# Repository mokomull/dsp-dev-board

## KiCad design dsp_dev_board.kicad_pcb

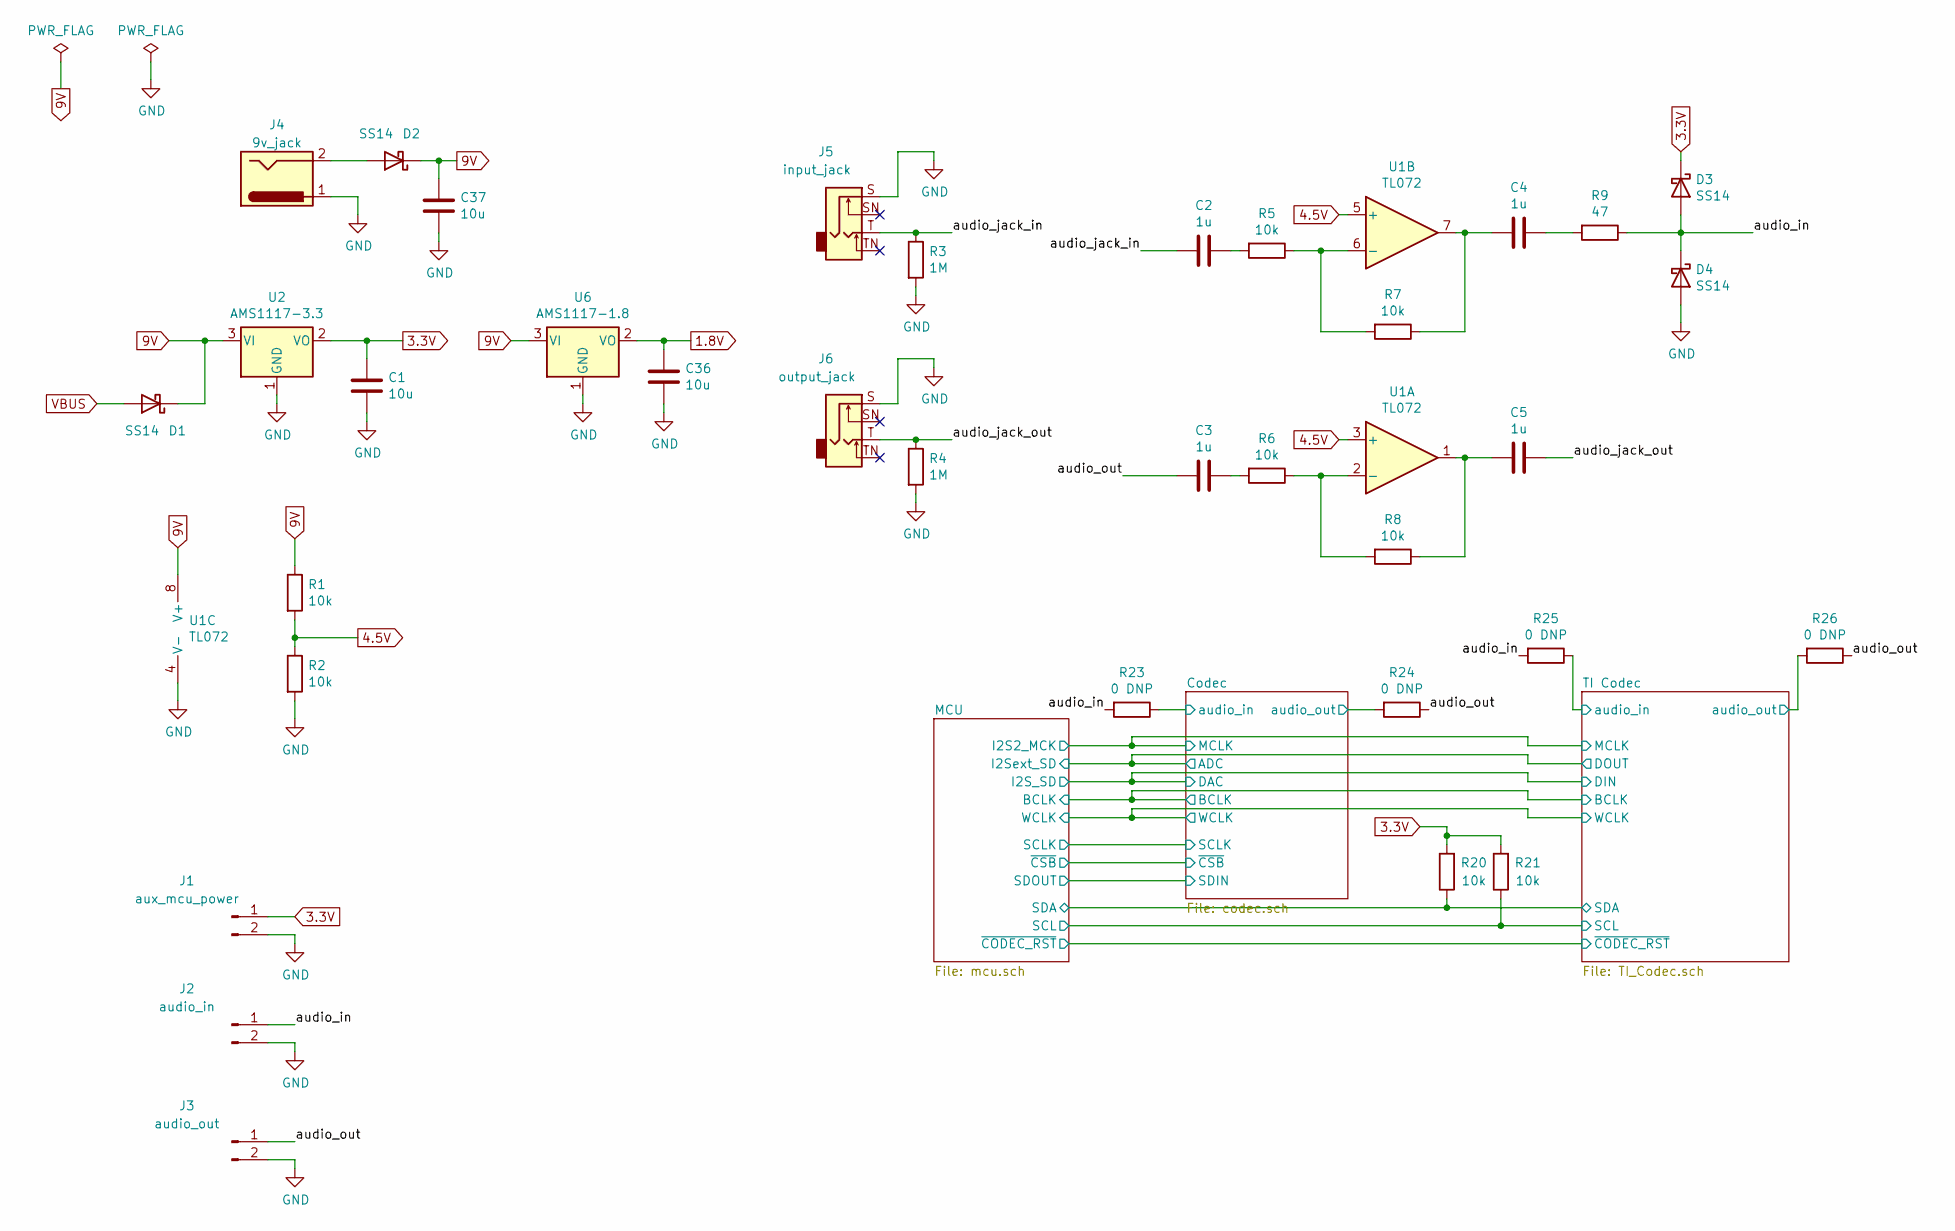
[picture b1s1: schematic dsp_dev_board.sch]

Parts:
C1, C36, C37: 10u; C_1206_3216Metric
C2, C3, C4, C5: 1u; C_0805_2012Metric
D1, D2, D3, D4: SS14; D_SMA
J1: aux_mcu_power; PinHeader_1x02_P2.54mm_Vertical
J2: audio_in; PinHeader_1x02_P2.54mm_Vertical
J3: audio_out; PinHeader_1x02_P2.54mm_Vertical
J4: 9v_jack; BarrelJack_Horizontal
J5: input_jack; Jack_6.35mm_Neutrik_NMJ4HCD2_Horizontal
J6: output_jack; Jack_6.35mm_Neutrik_NMJ4HCD2_Horizontal
R1, R2, R5, R6, R7, R8, R20, R21: 10k; R_0603_1608Metric
R3, R4: 1M; R_0603_1608Metric
R9: 47; R_0603_1608Metric
R23, R24, R25, R26: 0 DNP; R_0603_1608Metric
U1: TL072; SOIC-8_3.9x4.9mm_P1.27mm
U2: AMS1117-3.3; SOT-223-3_TabPin2
U6: AMS1117-1.8; SOT-223-3_TabPin2

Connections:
1.8V: C36.1, U6.2 (VO); also elsewhere on the board
3.3V: C1.1, D3.1 (K), J1.1, R20.2, R21.2, U2.2 (VO); also elsewhere on the board
4.5V: R1.2, R2.1, U1.3 (+), U1.5 (+)
9V: C37.1, D1.1 (K), D2.1 (K), R1.1, U1.8 (V+), U2.3 (VI), U6.3 (VI)
/Codec/audio_in: R23.1; also elsewhere on the board
/Codec/audio_out: R24.2; also elsewhere on the board
/MCU/SCL: R21.1; also elsewhere on the board
/MCU/SDA: R20.1; also elsewhere on the board
/TI Codec/audio_in: R25.1; also elsewhere on the board
/TI Codec/audio_out: R26.2; also elsewhere on the board
/audio_in: D3.2 (A), D4.1 (K), J2.1, R9.1, R23.2, R25.2
/audio_jack_in: C2.2, J5.T, R3.1
/audio_jack_out: C5.1, J6.T, R4.1
/audio_out: C3.2, J3.1, R24.1, R26.1
GND: C1.2, C36.2, C37.2, D4.2 (A), J1.2, J2.2, J3.2, J4.1, J5.S, J6.S, R2.2, R3.2, R4.2, U1.4 (V-), U2.1 (GND), U6.1 (GND); also elsewhere on the board
unnamed: C2.1, R5.2
unnamed: C3.1, R6.2
unnamed: C4.1, R9.2
unnamed: C4.2, R7.1, U1.7
unnamed: C5.2, R8.1, U1.1
unnamed: D2.2 (A), J4.2
unnamed: R5.1, R7.2, U1.6 (-)
unnamed: R6.1, R8.2, U1.2 (-)
VBUS: D1.2 (A); also elsewhere on the board

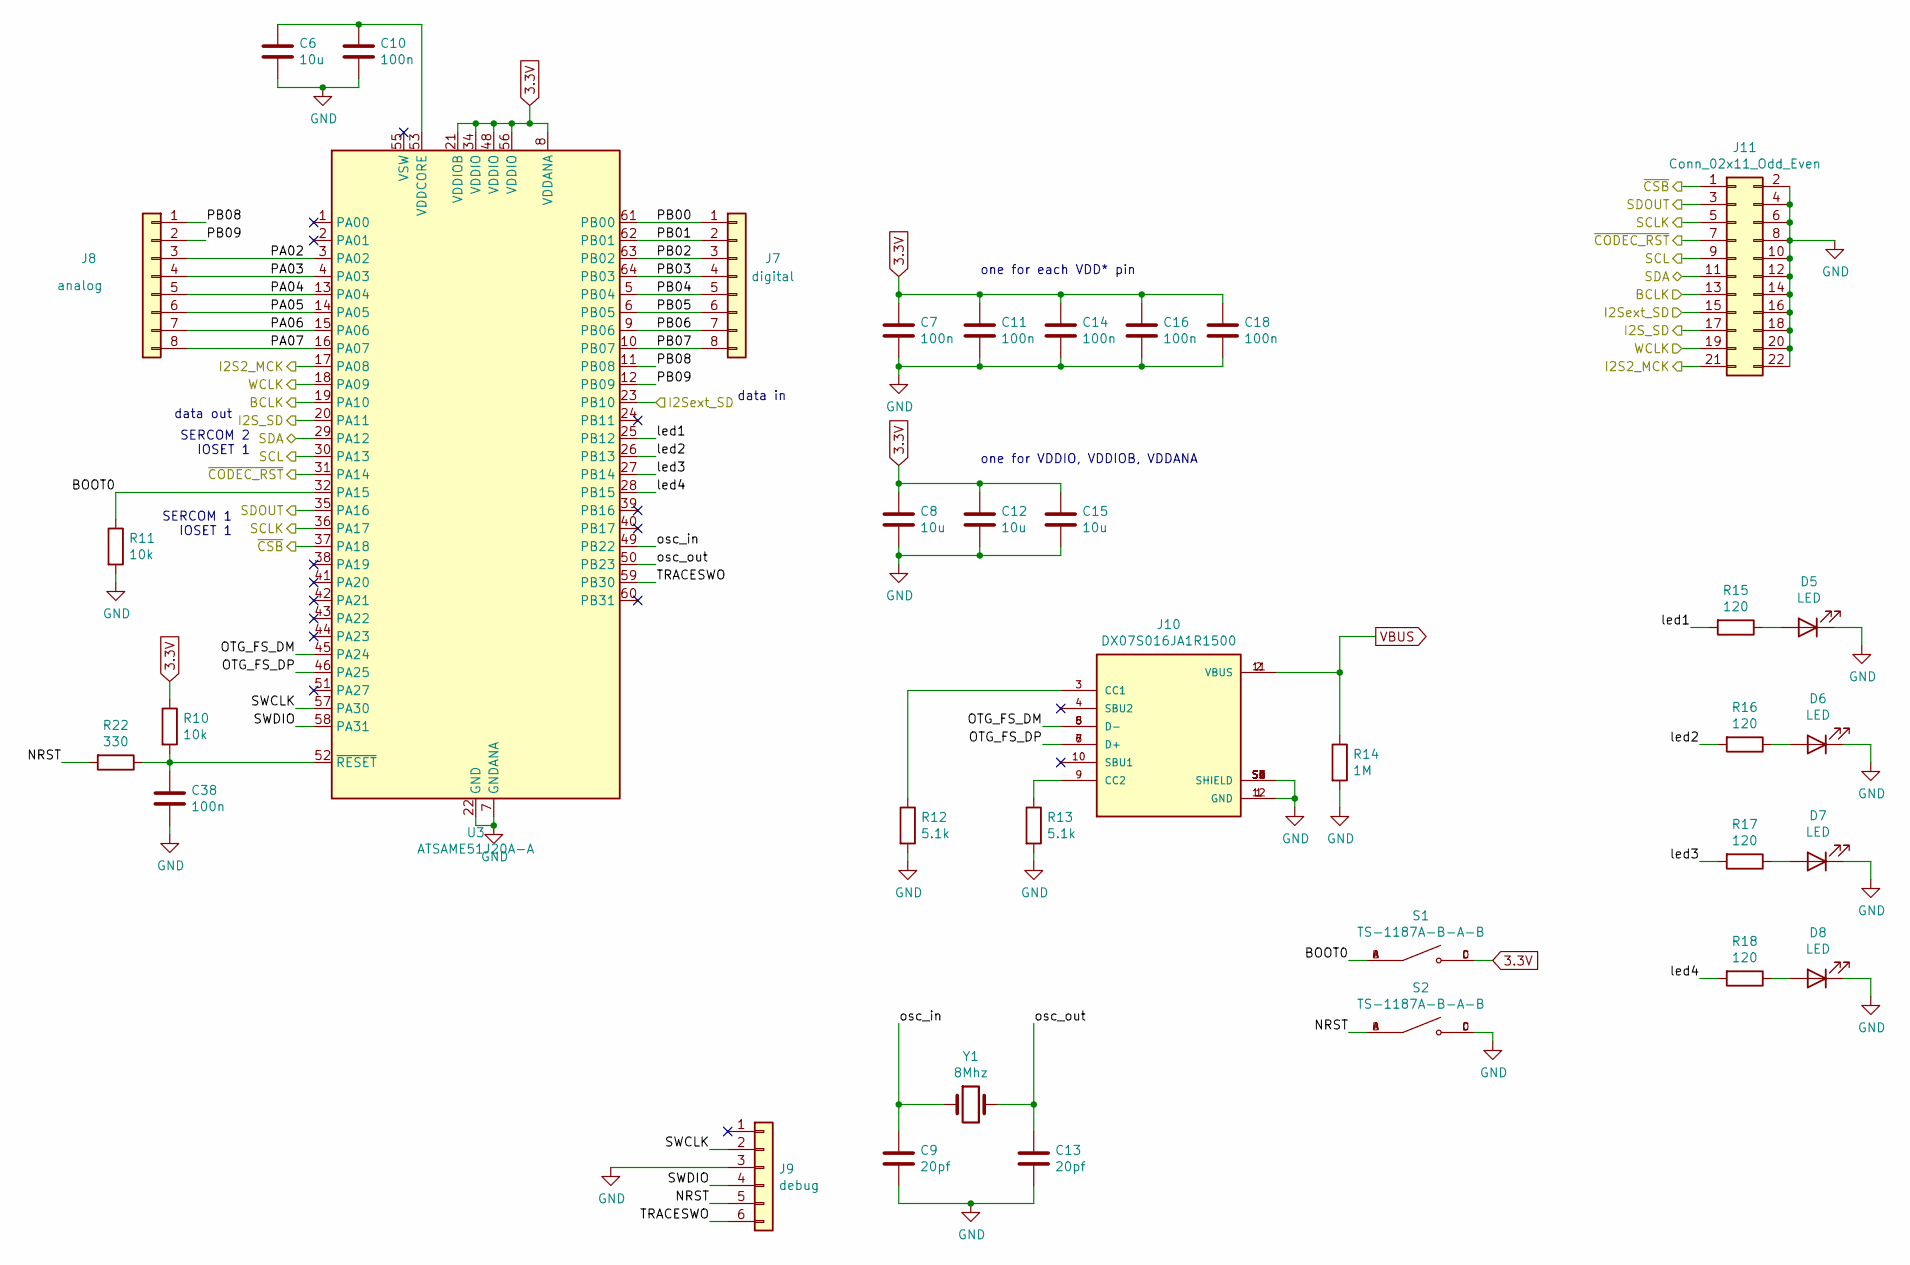
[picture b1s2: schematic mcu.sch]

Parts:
C6, C8, C12, C15: 10u; C_1206_3216Metric
C7, C10, C11, C14, C16, C18, C38: 100n; C_0603_1608Metric
C9, C13: 20pf; C_0603_1608Metric
D5, D6, D7, D8: LED; LED_0603_1608Metric
J7: digital; PinHeader_1x08_P2.54mm_Vertical
J8: analog; PinHeader_1x08_P2.54mm_Vertical
J9: debug; PinHeader_1x06_P2.54mm_Vertical
J10: DX07S016JA1R1500; JAE_DX07S016JA1R1500; PARTREV 1
J11: Conn_02x11_Odd_Even; PinHeader_2x11_P2.54mm_Vertical
R10, R11: 10k; R_0603_1608Metric
R12, R13: 5.1k; R_0603_1608Metric
R14: 1M; R_0603_1608Metric
R15, R16, R17, R18: 120; R_0603_1608Metric
R22: 330; R_0603_1608Metric
S1, S2: TS-1187A-B-A-B; SW_TS-1187A-B-A-B; PARTREV A0
U3: ATSAME51J20A-A; TQFP-64_10x10mm_P0.5mm
Y1: 8Mhz; Crystal_SMD_5032-2Pin_5.0x3.2mm

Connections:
3.3V: C7.1, C8.1, C11.1, C12.1, C14.1, C15.1, C16.1, C18.1, R10.1, S1.C, S1.D, U3.8 (VDDANA), U3.21 (VDDIOB), U3.34 (VDDIO), U3.48 (VDDIO), U3.56 (VDDIO); also elsewhere on the board
/Codec/ADC: J11.15, U3.23 (PB10); also elsewhere on the board
/Codec/BCLK: J11.13, U3.19 (PA10); also elsewhere on the board
/Codec/DAC: J11.17, U3.20 (PA11); also elsewhere on the board
/Codec/SCLK: J11.5, U3.36 (PA17); also elsewhere on the board
/Codec/SDIN: J11.3, U3.35 (PA16); also elsewhere on the board
/Codec/WCLK: J11.19, U3.18 (PA09); also elsewhere on the board
/Codec/~CSB: J11.1, U3.37 (PA18); also elsewhere on the board
/MCU/BOOT0: R11.1, S1.A, S1.B, U3.32 (PA15)
/MCU/I2S2_MCK: J11.21, U3.17 (PA08); also elsewhere on the board
/MCU/NRST: J9.5, R22.2, S2.A, S2.B
/MCU/OTG_FS_DM: J10.5 (D-), J10.8 (D-), U3.45 (PA24)
/MCU/OTG_FS_DP: J10.6 (D+), J10.7 (D+), U3.46 (PA25)
/MCU/PA02: J8.3, U3.3 (PA02)
/MCU/PA03: J8.4, U3.4 (PA03)
/MCU/PA04: J8.5, U3.13 (PA04)
/MCU/PA05: J8.6, U3.14 (PA05)
/MCU/PA06: J8.7, U3.15 (PA06)
/MCU/PA07: J8.8, U3.16 (PA07)
/MCU/PB00: J7.1, U3.61 (PB00)
/MCU/PB01: J7.2, U3.62 (PB01)
/MCU/PB02: J7.3, U3.63 (PB02)
/MCU/PB03: J7.4, U3.64 (PB03)
/MCU/PB04: J7.5, U3.5 (PB04)
/MCU/PB05: J7.6, U3.6 (PB05)
/MCU/PB06: J7.7, U3.9 (PB06)
/MCU/PB07: J7.8, U3.10 (PB07)
/MCU/PB08: J8.1, U3.11 (PB08)
/MCU/PB09: J8.2, U3.12 (PB09)
/MCU/SCL: J11.9, U3.30 (PA13); also elsewhere on the board
/MCU/SDA: J11.11, U3.29 (PA12); also elsewhere on the board
/MCU/SWCLK: J9.2, U3.57 (PA30)
/MCU/SWDIO: J9.4, U3.58 (PA31)
/MCU/TRACESWO: J9.6, U3.59 (PB30)
/MCU/led1: R15.2, U3.25 (PB12)
/MCU/led2: R16.2, U3.26 (PB13)
/MCU/led3: R17.2, U3.27 (PB14)
/MCU/led4: R18.2, U3.28 (PB15)
/MCU/osc_in: C9.1, U3.49 (PB22), Y1.1
/MCU/osc_out: C13.1, U3.50 (PB23), Y1.2
/MCU/~CODEC_RST: J11.7, U3.31 (PA14); also elsewhere on the board
GND: C6.2, C7.2, C8.2, C9.2, C10.2, C11.2, C12.2, C13.2, C14.2, C15.2, C16.2, C18.2, C38.2, D5.1 (K), D6.1 (K), D7.1 (K), D8.1 (K), J9.3, J10.1 (GND), J10.12 (GND), J10.S1 (SHIELD), J10.S2 (SHIELD), J10.S3 (SHIELD), J10.S4 (SHIELD), J10.S5 (SHIELD), J10.S6 (SHIELD), J11.2, J11.4, J11.6, J11.8, J11.10, J11.12, J11.14, J11.16, J11.18, J11.20, J11.22, R11.2, R12.2, R13.2, R14.2, S2.C, S2.D, U3.7 (GNDANA), U3.22 (GND), U3.33 (GND), U3.47 (GND), U3.54 (GND); also elsewhere on the board
unnamed: C6.1, C10.1, U3.53 (VDDCORE)
unnamed: C38.1, R10.2, R22.1, U3.52 (~RESET)
unnamed: D5.2 (A), R15.1
unnamed: D6.2 (A), R16.1
unnamed: D7.2 (A), R17.1
unnamed: D8.2 (A), R18.1
unnamed: J10.3 (CC1), R12.1
unnamed: J10.9 (CC2), R13.1
VBUS: J10.2 (VBUS), J10.11 (VBUS), R14.1; also elsewhere on the board

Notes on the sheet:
data out
data in
one for each VDD* pin
one for VDDIO, VDDIOB, VDDANA
SERCOM 1 IOSET 1
SERCOM 2 IOSET 1

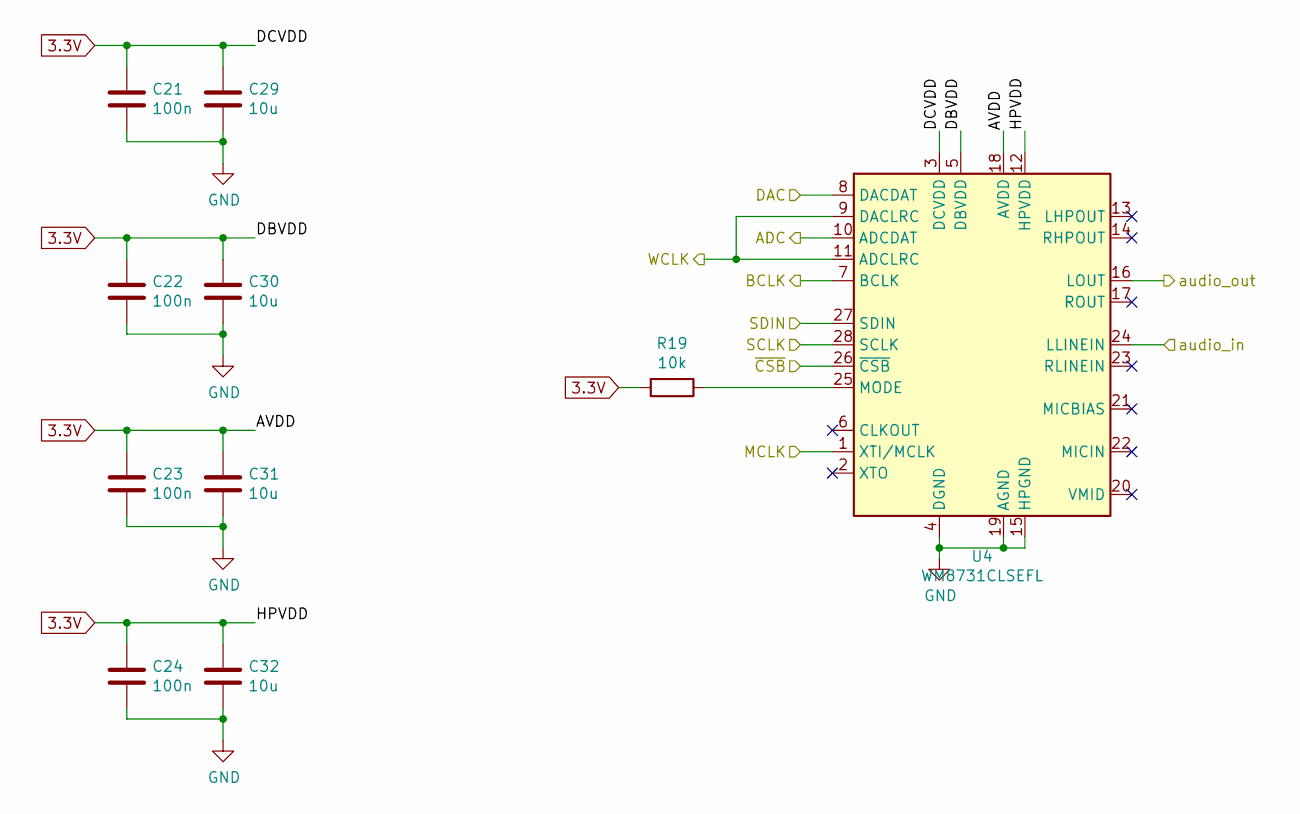
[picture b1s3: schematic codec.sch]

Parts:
C21, C22, C23, C24: 100n; C_0603_1608Metric
C29, C30, C31, C32: 10u; C_1206_3216Metric
R19: 10k; R_0603_1608Metric
U4: WM8731CLSEFL; QFN-28-1EP_5x5mm_P0.5mm_EP3.35x3.35mm

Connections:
3.3V: C21.1, C22.1, C23.1, C24.1, C29.1, C30.1, C31.1, C32.1, R19.2, U4.3 (DCVDD), U4.5 (DBVDD), U4.12 (HPVDD), U4.18 (AVDD); also elsewhere on the board
/Codec/ADC: U4.10 (ADCDAT); also elsewhere on the board
/Codec/BCLK: U4.7 (BCLK); also elsewhere on the board
/Codec/DAC: U4.8 (DACDAT); also elsewhere on the board
/Codec/SCLK: U4.28 (SCLK); also elsewhere on the board
/Codec/SDIN: U4.27 (SDIN); also elsewhere on the board
/Codec/WCLK: U4.9 (DACLRC), U4.11 (ADCLRC); also elsewhere on the board
/Codec/audio_in: U4.24 (LLINEIN); also elsewhere on the board
/Codec/audio_out: U4.16 (LOUT); also elsewhere on the board
/Codec/~CSB: U4.26 (~CSB); also elsewhere on the board
/MCU/I2S2_MCK: U4.1 (XTI/MCLK); also elsewhere on the board
GND: C21.2, C22.2, C23.2, C24.2, C29.2, C30.2, C31.2, C32.2, U4.4 (DGND), U4.15 (HPGND), U4.19 (AGND), U4.29 (AGND); also elsewhere on the board
unnamed: R19.1, U4.25 (MODE)

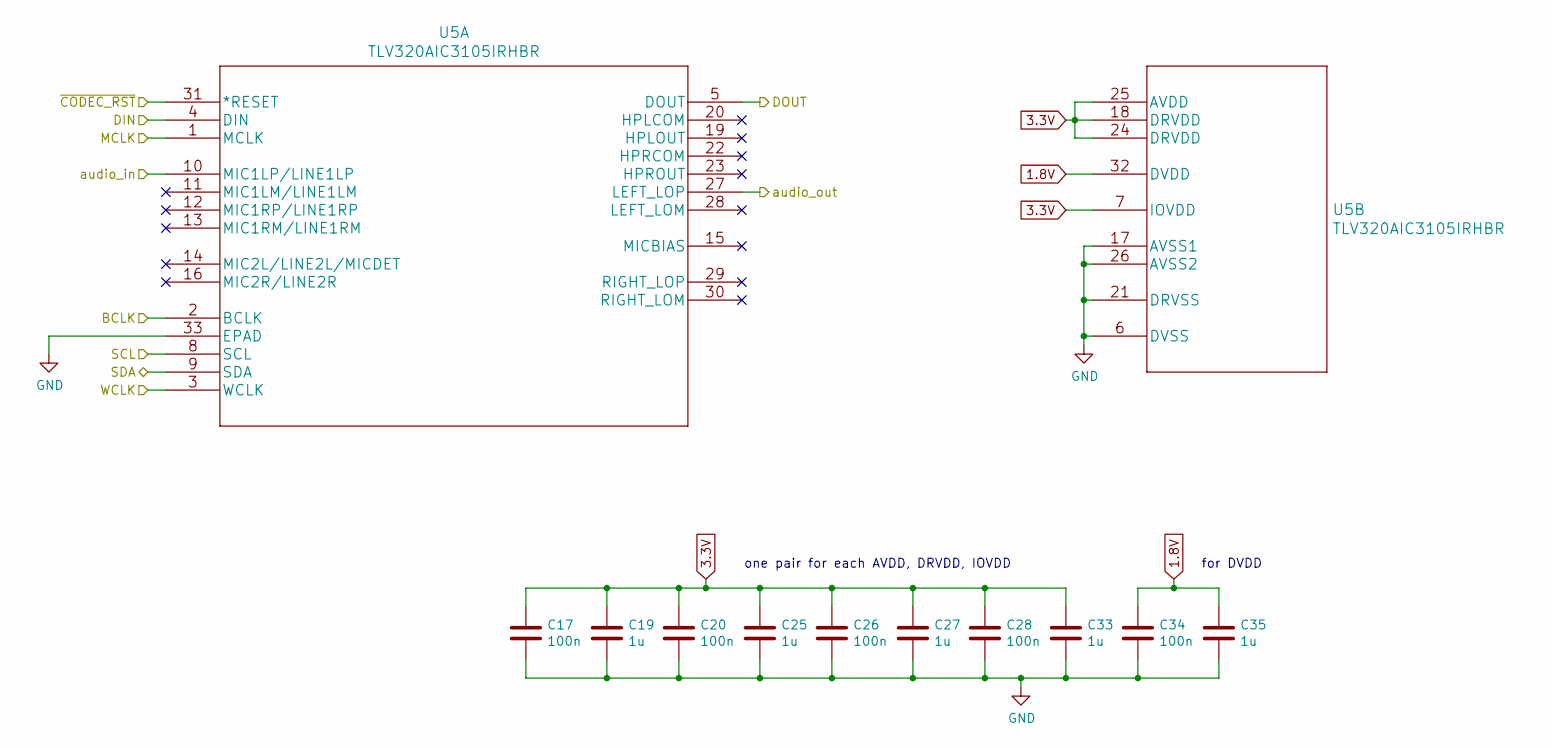
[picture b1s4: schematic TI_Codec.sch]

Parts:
C17, C20, C26, C28, C34: 100n; C_0603_1608Metric
C19, C25, C27, C33, C35: 1u; C_0805_2012Metric
U5: TLV320AIC3105IRHBR; QFN-32-1EP_5x5mm_P0.5mm_EP3.45x3.45mm_ThermalVias

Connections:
1.8V: C34.1, C35.1, U5.32 (DVDD); also elsewhere on the board
3.3V: C17.1, C19.1, C20.1, C25.1, C26.1, C27.1, C28.1, C33.1, U5.7 (IOVDD), U5.18 (DRVDD), U5.24 (DRVDD), U5.25 (AVDD); also elsewhere on the board
/Codec/ADC: U5.5 (DOUT); also elsewhere on the board
/Codec/BCLK: U5.2 (BCLK); also elsewhere on the board
/Codec/DAC: U5.4 (DIN); also elsewhere on the board
/Codec/WCLK: U5.3 (WCLK); also elsewhere on the board
/MCU/I2S2_MCK: U5.1 (MCLK); also elsewhere on the board
/MCU/SCL: U5.8 (SCL); also elsewhere on the board
/MCU/SDA: U5.9 (SDA); also elsewhere on the board
/MCU/~CODEC_RST: U5.31 (*RESET); also elsewhere on the board
/TI Codec/audio_in: U5.10 (MIC1LP/LINE1LP); also elsewhere on the board
/TI Codec/audio_out: U5.27 (LEFT_LOP); also elsewhere on the board
GND: C17.2, C19.2, C20.2, C25.2, C26.2, C27.2, C28.2, C33.2, C34.2, C35.2, U5.6 (DVSS), U5.17 (AVSS1), U5.21 (DRVSS), U5.26 (AVSS2), U5.33 (EPAD); also elsewhere on the board

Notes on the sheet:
one pair for each AVDD, DRVDD, IOVDD
for DVDD

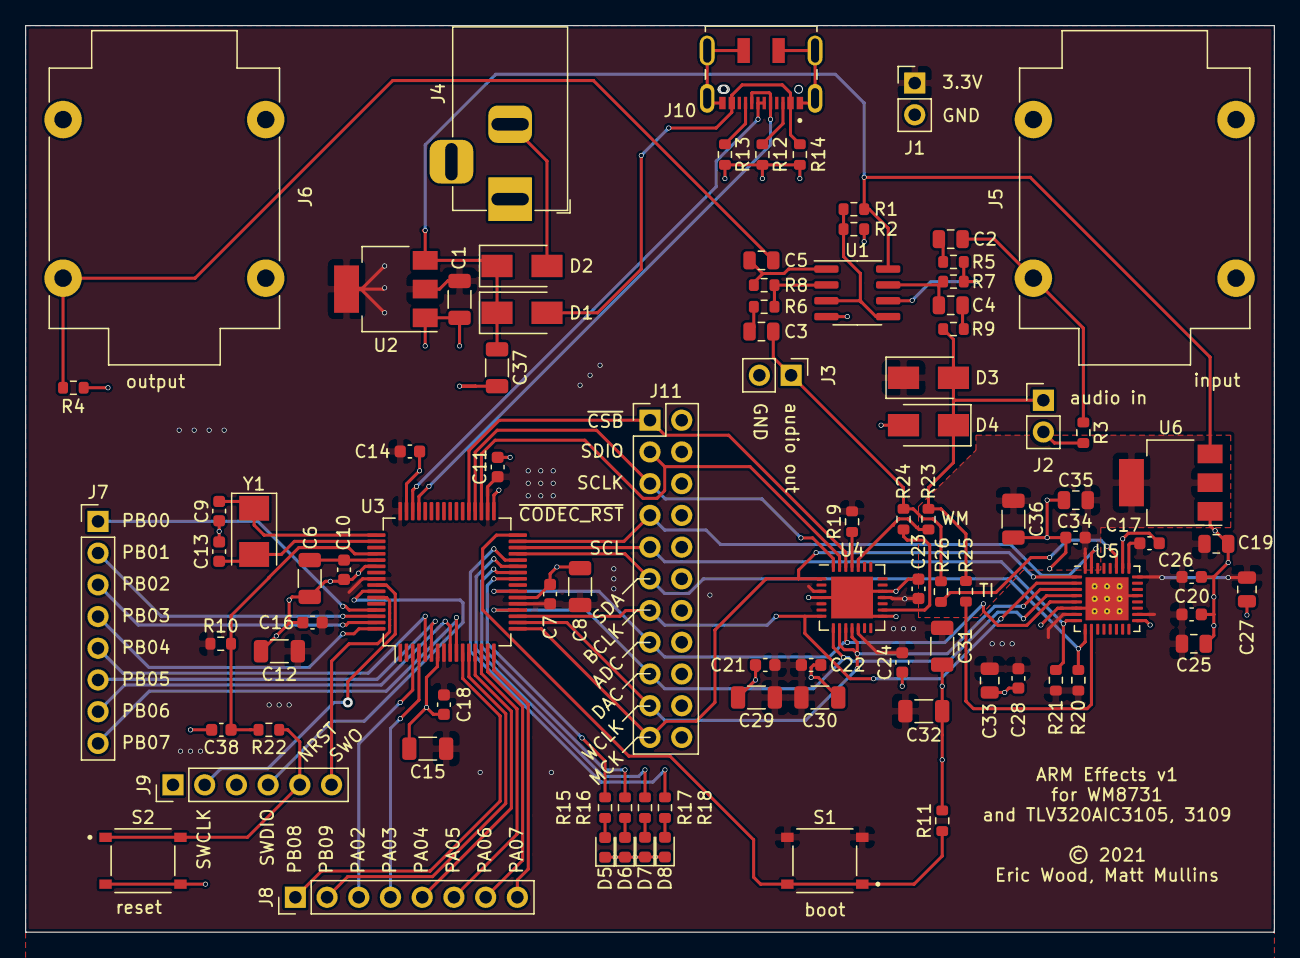
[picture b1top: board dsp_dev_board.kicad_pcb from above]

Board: 4 copper layers, 100.0 x 72.6 mm, 92 parts (0 on the bottom side), 71 nets.

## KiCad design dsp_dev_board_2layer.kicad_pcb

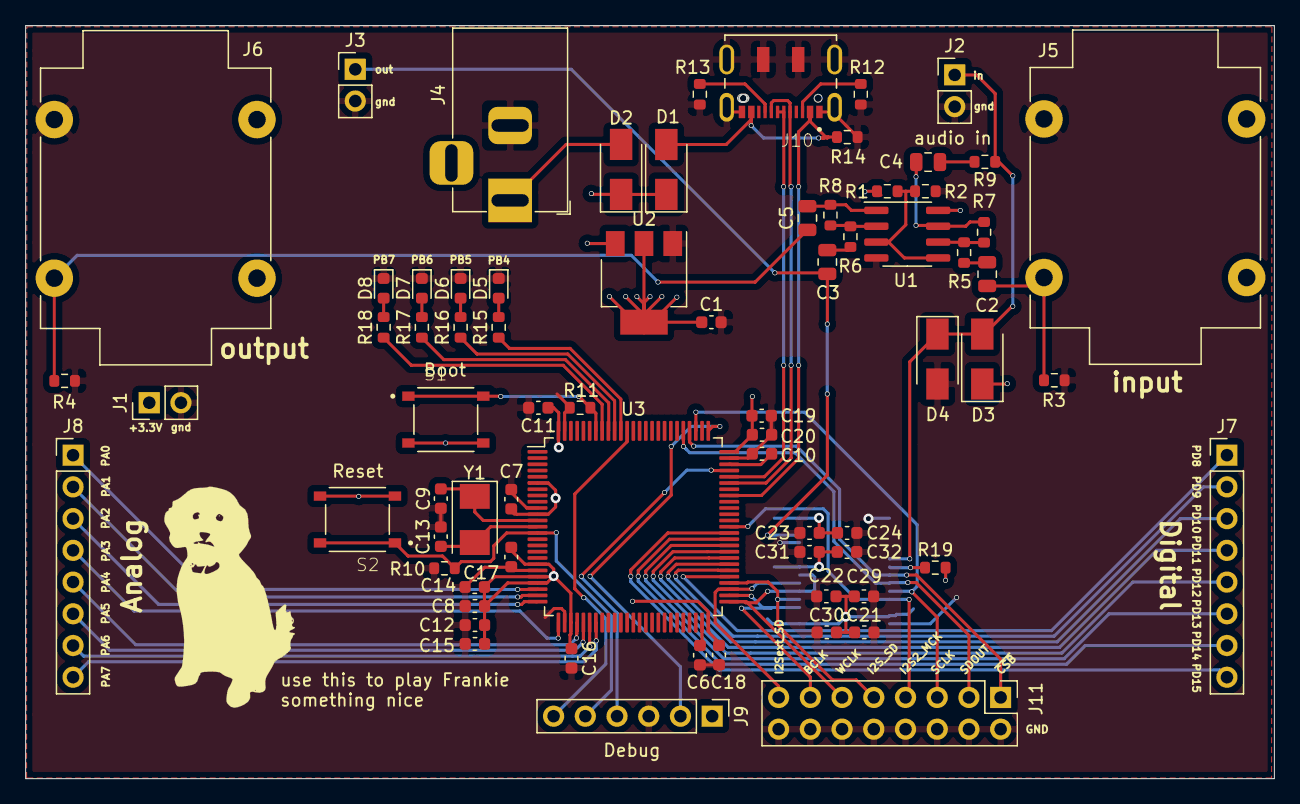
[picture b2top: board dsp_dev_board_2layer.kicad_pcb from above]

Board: 2 copper layers, 100.0 x 60.3 mm, 73 parts (1 on the bottom side), 63 nets.

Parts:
C1, C21, C22, C23, C24: 0.1u; C_0603_1608Metric
C2, C3, C4, C5: 1u; C_0805_2012Metric
C6, C10: 2.2u; C_0603_1608Metric
C7, C11, C12, C14, C16, C17, C18, C19: 100n; C_0603_1608Metric
C8, C15: 1u; C_0603_1608Metric
C9, C13: 20pf; C_0603_1608Metric
C20: 4.7u; C_0603_1608Metric
C29, C30, C31, C32: 10u; C_0603_1608Metric
D1, D2, D3, D4: SS14; D_SMA
D5, D6, D7, D8: LED; LED_0603_1608Metric
J1: aux_mcu_power; PinHeader_1x02_P2.54mm_Vertical
J2: audio_in; PinHeader_1x02_P2.54mm_Vertical
J3: audio_out; PinHeader_1x02_P2.54mm_Vertical
J4: 9v_jack; BarrelJack_Horizontal
J5: input_jack; Jack_6.35mm_Neutrik_NMJ4HCD2_Horizontal
J6: output_jack; Jack_6.35mm_Neutrik_NMJ4HCD2_Horizontal
J7: PD8-15 (digital); PinHeader_1x08_P2.54mm_Vertical
J8: PA0-7 (analog); PinHeader_1x08_P2.54mm_Vertical
J9: debug; PinHeader_1x06_P2.54mm_Vertical
J10: DX07S016JA1R1500; JAE_DX07S016JA1R1500
J11: Conn_02x08_Odd_Even; PinHeader_2x08_P2.54mm_Vertical
R1, R2, R5, R6, R7, R8, R10, R11, R19: 10k; R_0603_1608Metric
R3, R4, R14: 1M; R_0603_1608Metric
R9: 47; R_0603_1608Metric
R12, R13: 5.1k; R_0603_1608Metric
R15, R16, R17, R18: 120; R_0603_1608Metric
S1, S2: TS-1187A-B-A-B; SW_TS-1187A-B-A-B
U1: TL072; SOIC-8_3.9x4.9mm_P1.27mm
U2: AMS1117-3.3; SOT-223-3_TabPin2
U3: STM32F407VETx; LQFP-100_14x14mm_P0.5mm
U4: WM8731SEDS; SSOP-28_5.3x10.2mm_P0.65mm
Y1: 8Mhz; Crystal_SMD_5032-2Pin_5.0x3.2mm

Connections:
3.3V: C1.1, C7.1, C8.1, C11.1, C12.1, C14.1, C15.1, C16.1, C17.1, C18.1, C19.1, C20.1, C21.1, C22.1, C23.1, C24.1, C29.1, C30.1, C31.1, C32.1, D3.1, J1.1, R19.2, S1.C, S1.D, S2.C, S2.D, U2.2, U3.6, U3.11, U3.19, U3.21, U3.22, U3.28, U3.50, U3.75, U3.100, U4.1, U4.8, U4.14, U4.27
4.5V: R1.2, R2.1, U1.3, U1.5
9V: D1.1, D2.1, R1.1, U1.8, U2.3
/Codec/ADC: J11.15, U3.53, U4.6
/Codec/BCLK: J11.13, U3.52, U4.3
/Codec/DAC: J11.9, U3.54, U4.4
/Codec/SCLK: J11.5, U3.78, U4.24
/Codec/SDIN: J11.3, U3.80, U4.23
/Codec/WCLK: J11.11, U3.51, U4.5, U4.7
/Codec/~CSB: J11.1, U3.79, U4.22
/MCU/BOOT0: R11.1, S1.A, S1.B, U3.94
/MCU/I2S2_MCK: J11.7, U3.63, U4.25
/MCU/NRST: J9.5, R10.1, S2.A, S2.B, U3.14
/MCU/OTG_FS_DM: J10.5, J10.8, U3.70
/MCU/OTG_FS_DP: J10.6, J10.7, U3.71
/MCU/SWCLK: J9.2, U3.76
/MCU/SWDIO: J9.4, U3.72
/MCU/TRACESWO: J9.6, U3.89
/MCU/VCAP_1: C6.1, U3.49
/MCU/VCAP_2: C10.1, U3.73
/MCU/led1: R15.2, U3.90
/MCU/led2: R16.2, U3.91
/MCU/led3: R17.2, U3.92
/MCU/led4: R18.2, U3.93
/MCU/osc_in: C9.1, U3.12, Y1.1
/MCU/osc_out: C13.1, U3.13, Y1.2
/audio_in: D3.2, D4.1, J2.1, R9.1, U4.20
/audio_jack_in: C2.2, J5.T, R3.1
/audio_jack_out: C5.1, J6.T, R4.1
/audio_out: C3.2, J3.1, U4.12
GND: C1.2, C6.2, C7.2, C8.2, C9.2, C10.2, C11.2, C12.2, C13.2, C14.2, C15.2, C16.2, C17.2, C18.2, C19.2, C20.2, C21.2, C22.2, C23.2, C24.2, C29.2, C30.2, C31.2, C32.2, D4.2, D5.1, D6.1, D7.1, D8.1, J1.2, J2.2, J3.2, J4.2, J5.S, J6.S, J9.3, J10.1, J10.12, J10.S1, J10.S2, J10.S3, J10.S4, J10.S5, J10.S6, J11.2, J11.4, J11.6, J11.8, J11.10, J11.12, J11.14, J11.16, R2.2, R3.2, R4.2, R10.2, R11.2, R12.2, R13.2, R14.2, U1.4, U2.1, U3.10, U3.20, U3.27, U3.74, U3.99, U4.11, U4.15, U4.28
unnamed: C2.1, R5.2
unnamed: C3.1, R6.2
unnamed: C4.1, R9.2
unnamed: C4.2, R7.1, U1.7
unnamed: C5.2, R8.1, U1.1
unnamed: D2.2, J4.1
unnamed: D5.2, R15.1
unnamed: D6.2, R16.1
unnamed: D7.2, R17.1
unnamed: D8.2, R18.1
unnamed: J7.1, U3.55
unnamed: J7.2, U3.56
unnamed: J7.3, U3.57
unnamed: J7.4, U3.58
unnamed: J7.5, U3.59
unnamed: J7.6, U3.60
unnamed: J7.7, U3.61
unnamed: J7.8, U3.62
unnamed: J8.1, U3.23
unnamed: J8.2, U3.24
unnamed: J8.3, U3.25
unnamed: J8.4, U3.26
unnamed: J8.5, U3.29
unnamed: J8.6, U3.30
unnamed: J8.7, U3.31
unnamed: J8.8, U3.32
unnamed: J10.3, R12.1
unnamed: J10.9, R13.1
unnamed: R5.1, R7.2, U1.6
unnamed: R6.1, R8.2, U1.2
unnamed: R19.1, U4.21
VBUS: D1.2, J10.2, J10.11, R14.1, U3.68

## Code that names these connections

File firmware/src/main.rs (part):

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    let pins = atsamd_hal::gpio::v2::Pins::new(peripherals.PORT);

    let control_pads = spi::Pads::<Sercom1, IoSet1>::new()
        .data_out::<Pad0, _>(pins.pa16)
        .sclk(pins.pa17);

    let control_spi = spi::Config::new(
        &mut peripherals.MCLK,
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    .baud(100.khz())
    .enable();

    let control_csb = pins.pa18.into_push_pull_output();

    let mut control = Control {
        spi: control_spi,
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    // enable output
    control.set_register(WM8731::power_down(final_power_settings));

    let _mck = pins.pa08.into_alternate::<J>();
    let _sck = pins.pa10.into_alternate::<J>();
    let _dac = pins.pa11.into_alternate::<J>();
    let _ws = pins.pa09.into_alternate::<J>();

    let i2s = peripherals.I2S;
    i2s.clkctrl[0].write(|w| {
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
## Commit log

2021-01-14 Initial commit, power section seems ok?
2021-01-15 Add codec symbol
2021-01-17 Wire up codec
2021-01-17 Hook up peripherals
2021-01-17 Add debug header
2021-01-18 Use a better codec
2021-01-20 Power the MCU
2021-01-24 Coupling caps, crystals
2021-01-24 Clean things up, add LEDs, aux stuff
2021-02-13 Various fixes
2021-02-13 Add debug interface
2021-02-13 Add traces
2021-02-14 Use contiguous GPIO pins
2021-02-14 Improved probe points
2021-02-14 Assign a bunch of footprints
2021-02-14 Add tactile switch footprints
2021-02-14 Move switch library here
2021-02-14 Add USB connector
2021-02-14 unfuck symbols
2021-02-14 maybe this will work
2021-02-14 make routing easier
2021-02-14 Update pins for actual ADC ins
2021-02-15 those two need to be connected
2021-02-27 just a buncha stuff
2021-02-28 Progress
2021-02-28 USB to go
2021-02-28 Lots of cleanup
2021-03-07 Basically done?
2021-03-07 it's done
2021-04-13 4 layer progress
2021-04-13 mcu.sch: replace microcontroller with SAME51J
    The I2S bus is placed according to IOSET 1.
    The ADC inputs are sprinkled around mostly-arbitrarily, but since
    PA00-01 are not connected to either ADC peripheral, this uses PB08-09
    for those two signals. PB08 and 09 are connected to *both* ADCs, so
    they should be sampleable simultaneously if necessary.
2021-04-15 Wire up SPI control, add TLV320AIC310x and I2C
    The I2C is convenient: if I got it backwards, the SDA and SCL pins are
    reversed between SERCOM 2 and 4.
2021-04-15 Add pull-up resistors for I2C
2021-04-15 mcu: swap 4.7u VDDCORE cap (C6) for 10u
    There's already 10u all over the board so why not squeeze a bit more out
    of the BOM.
    Also adds a footprint for the 100n next to it (C10).
2021-04-15 Apply footprint-finder's suggestion for USB-C
    It likes the USB_C: prefix, I guess.
2021-04-15 "0.1u" -> "100n"; use 1206 10u for bulk decoupling
    The 1206 size has a much better derating-vs-bias-voltage curve.
2021-04-15 Add a 10u decoupling for the main 9V supply
2021-04-15 Wire up more internal buses to the debug connector
    It'll be nice to scope the I2C bus as well.
2021-04-15 Add RC to NRST for timing
    The Schematic Checklist, §60.4 "External Reset Circuit" told me to do
    it.
2021-04-15 re-import USB-C connector
2021-04-16 sch: add jumpers to select audio path
    This way the unused codec's audio path won't be dangling as an antenna
    picking up unnecessary noise on the analog side
2021-04-19 Add TI codec schematic page.
    This has actually already gone through a couple revisions, but I never
    added it to git. Oops.
2021-04-19 PCB: most major layout with both codec footprints
    Surprisingly, I don't hate the really long I2S bus-like formation
    between both footprints, though it does break up both the front and back
    layers in the same orientation.
2021-04-19 Annotate schematic symbols
    I forgot to do this when I added the jumper resistors.
2021-04-19 PCB: update TI's footprint so thermal vias are GND
    They were numbered "V" which KiCad thought should be a different net,
    throwing all sorts of DRC errors. Numbering them all 33 makes it act
    like the built-in footprint with thermal vias.
2021-04-21 Use actual parts from Mouser order
    I was able to order the ATSAME51J20A-AU and the WM8731CLSEFL.
2021-04-24 WIP: QFN all the things
2021-04-29 pcb: everything connected, passes DRC
2021-04-29 pcb: enhance bypassing on the left side of MCU
    I stuck the bulk bypassing for VDDIO near pin 56, so nudge those
    capacitors over so the F.Cu layer can connect them, and stitch that
    through with some vias to the B.Cu +3.3V rail.
2021-04-29 pcb: nudge stuff around so it looks good
2021-04-29 pcb: move silkscreens so they're visible
    Component references should not be over vias or other parts. Move them
    so they're visible, but maintain orientation -- the label is vertical if
    the component is vertical.
2021-04-29 pcb: add silkscreens
    This labels the pins for the analog, digital, debug, and probepoint
    headers. I also moved R10 so I could have more room for the digital
    header labels.
2021-04-30 pcb: move silkscreen for C1 and C26
    They were under other components.
2021-04-30 pcb: minor movements, add more labels
    more silkscreens, move some traces
2021-04-30 Swap TI codec footprint for builtin QFN
    5x5mm size, 0.5mm pitch, 3.45mm exposed pad. TI recommends the thermal
    vias, though on something this low-power, I think that's overkill.
    I had to use a copper-fill keepout and manually draw traces to keep the
    pads from being horribly misshaped.
2021-04-30 pcb: move more silkscreens
    I moved C17, so its silkscreen ended up under C19.
    Label the jumpers for WM and TI codecs (and abbreviate to WM because
    "WM8731" doesn't fit in the space I have)
2021-04-30 power should be center-negative
    And add attribution text to the PCB
2021-04-30 add boot/reset labels for the switches
2021-04-30 fab: add fab files from first board order
2021-05-18 firmware: cortex-m-quickstart + empty loop
    This seems to work!
2021-05-18 firmware: blink LED1 at 2Hz
    It works!
2021-05-19 fw: blink all LEDs in order
2021-05-19 fw: send "hello, world." over SPI
    This will be the configuration channel for the WM8731 codec.
2021-05-19 fw: transmit bit pattern with I2S
    This results in a jittery, but exactly 12.288MHz MCLK, and 48.000kHz
    WCLK.
2021-05-19 fw: import WM8731 configuration from echo_pedal
    This is pretty much an exact copy/paste from the echo-pedal experiment,
    with `use` glue to make the names match up exactly as written
    previously.
    It does not quite work, though.
2021-05-31 fw: work around not-actually-blocking SPI impl
    The atsamd_hal blocking SPI implementation blocks until it's in the
    FIFO, not until it's been transmitted. This results in #CS being
    deasserted way too early for the first command, so instead just wait
    long enough to get the command out.
2021-05-31 fw: mono mode still needs txdata to be written
    It seems to ignore the 0 written here (verified with an oscilloscope),
    and does dutifully copy the left channel to the corresponding right
    channel timeslot. But without writing *anything* it eats
    every-other-sample and I was getting 2kHz instead of 1kHz.

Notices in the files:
dsp_dev_board.kicad_pcb:
© 2021
